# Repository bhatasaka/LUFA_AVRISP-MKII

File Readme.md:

# **LUFA AVRISP-MKII**

**Custom PCB designed for the LUFA AVRISP-MKII Project https://github.com/abcminiuser/lufa**

This repo contains the PCB and firmware configuration files for a compact USB-C programming board designed for LUFA's AVRISP-MKII firmware based on an ATMega16u2.  Major thanks to the LUFA project for making this possible!

<div align="center">

</div>

## About
---
This PCB is designed only for ISP. However, the PCB could be expanded to break out the PDI and TPI pins as well! It has a level shifter that allows programming of targets other than 5V. Adding a 2-pin jumper to `V Targ` allows the target device to be powered from this board as well. 2 voltages are available - 5v and 3.3v. If you wish to program the 16u2 from the ISP header, the RST pin must be shorted to the 16u2's RST pin, this can be done with a jumper on the `Self Prog` pin header.
## File Structure
---
- `Firmware`
    - Contains configuration files for the LUFA AVRISP-MKII project.
- `KiCad`
    - Contains the KiCad files for the PCB.
- `images`
    - Contains images of the PCB and schematic.

## Firmware Setup and Programming
---
### Setup
1. Clone the repository from https://github.com/abcminiuser/lufa.
1. From this repo's `Firmware` folder, copy and replace the `Config` folder and `makefile` into `Projects/AVRISP-MKII/` in the LUFA repo.
1. From this repo's `Firmware` folder, copy `BHATASAKA` folder into`LUFA/Divers/Board/AVR8` in the LUFA repo.
1. In the LUFA repo, modify `LUFA/Drivers/Board/Board.h` and copy the last `#elif`, then modify it to use `BHATASAKA` as the board name.
1. In the LUFA repo, modify `LUFA/Drivers/Board/LEDs.h` and copy the last `#elif`, then modify it to use `BHATASAKA` as the board name.

### Compiling
Go to `Projects/AVRISP-MKII/` and type `make`. Make sure Make and avr-gcc are installed and in your path.

### Programming
1. The hex file generated in the `Projects/AVRISP-MKII/` folder can be flashed through DFU. Plug the board into your computer. If it is blank it will show up as ATMega 16u2. If it doesn't, reset the chip after it's plugged in.
1. Download Zadig (https://zadig.akeo.ie/) and Atmel Flip (https://www.microchip.com/en-us/development-tool/flip) - make sure you Java SE JRE installed and in your path. Install Flip.
1. Open Zadig and select the 16u2. Install the `libusb-win32` driver for the chip.
1. Open Atmel Flip, select the 16u2, connect to it, load the hex file, and program the chip. It should now show up as an AVRISP-MKII (may need to unplug and replug).

## Usage
---
Install AVRISP-MKII drivers with Zadig (https://zadig.akeo.ie/). Choose `libusb-win32`.
To use with Arduino, select the `AVRISP mkii` programmer. To use with AVRDude, use `-c avrispmkII`.

---
Major thanks to LUFA, KiCad, and Zadig!

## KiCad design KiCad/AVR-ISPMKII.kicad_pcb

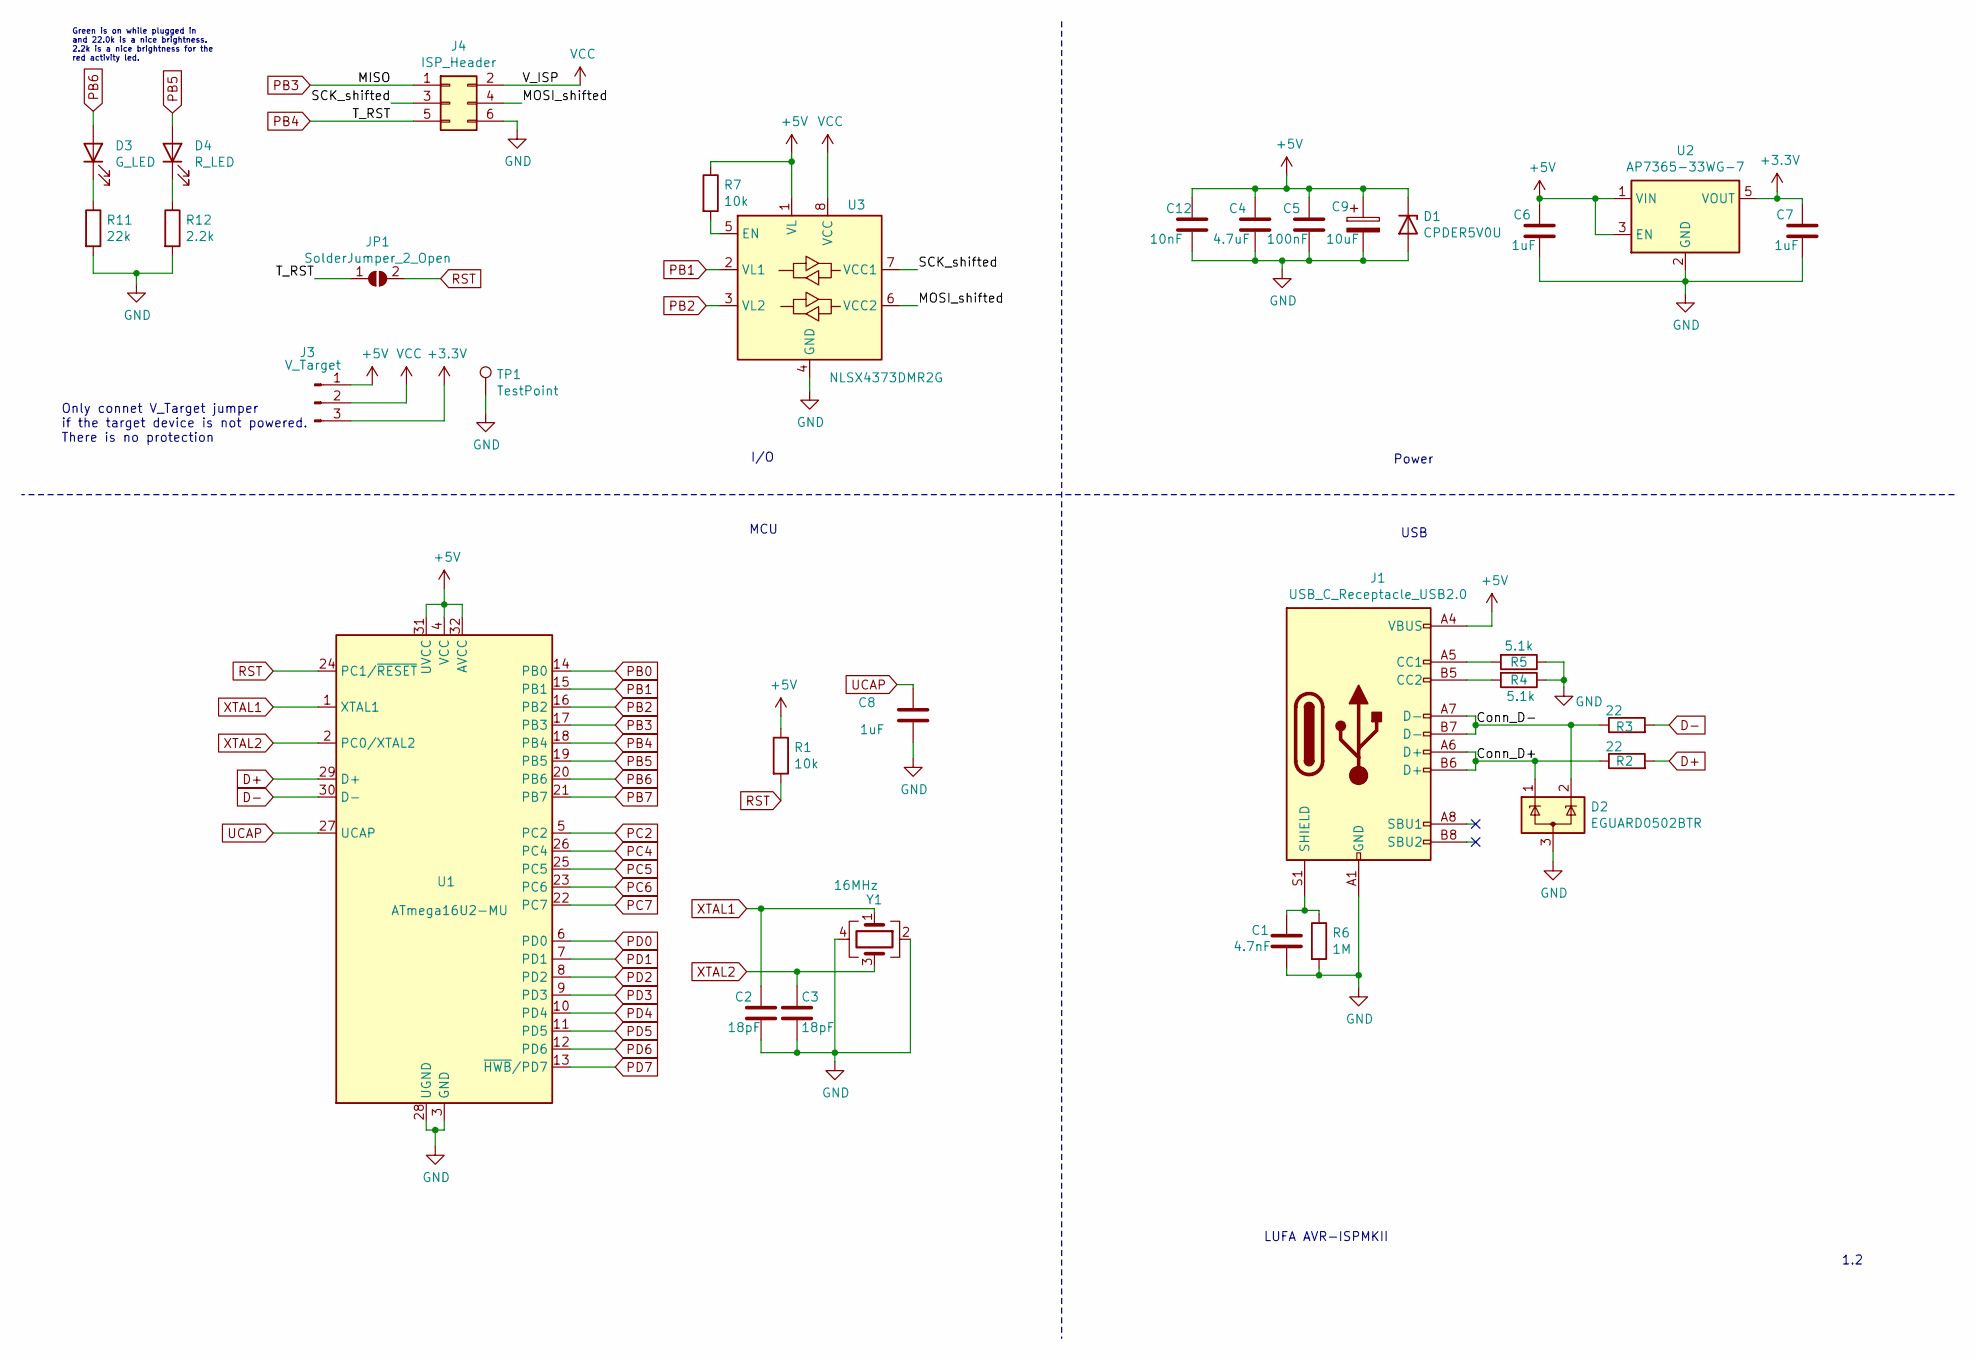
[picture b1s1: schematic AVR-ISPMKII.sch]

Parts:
C1: 4.7nF; C_0603_1608Metric
C2, C3: 18pF; C_0402_1005Metric
C4: 4.7uF; C_0805_2012Metric
C5: 100nF; C_0603_1608Metric
C6, C7, C8: 1uF; C_0603_1608Metric
C9: 10uF; C_0805_2012Metric
C12: 10nF; C_0603_1608Metric
D1: CPDER5V0U; D_0402_1005Metric
D2: EGUARD0502BTR; SOT-523
D3: G_LED; LED_0603_1608Metric
D4: R_LED; LED_0603_1608Metric
J1: USB_C_Receptacle_USB2.0; USB_C_Receptacle_HRO_TYPE-C-31-M-12
J3: V_Target; PinHeader_1x03_P2.54mm_Vertical
J4: ISP_Header; PinHeader_2x03_P2.54mm_Vertical
JP1: SolderJumper_2_Open; SolderJumper-2_P1.3mm_Open_TrianglePad1.0x1.5mm
R1, R7: 10k; R_0603_1608Metric
R2, R3: 22; R_0603_1608Metric
R4, R5: 5.1k; R_0603_1608Metric
R6: 1M; R_0603_1608Metric
R11: 22k; R_0603_1608Metric
R12: 2.2k; R_0603_1608Metric
TP1: TestPoint; TestPoint_Pad_D2.0mm
U1: ATmega16U2-MU; QFN-32-1EP_5x5mm_P0.5mm_EP3.1x3.1mm
U2: AP7365-33WG-7; TSOT-23-5
U3: NLSX4373DMR2G; TSSOP8
Y1: 16MHz; Crystal_SMD_2520-4Pin_2.5x2.0mm

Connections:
+3V3: C7.1, J3.3, U2.5 (VOUT)
+5V: C4.1, C5.1, C6.1, C9.1, C12.1, D1.1 (K), J1.A4 (VBUS), J1.A9 (VBUS), J1.B4 (VBUS), J1.B9 (VBUS), J3.1, R1.1, R7.1, U1.4 (VCC), U1.31 (UVCC), U1.32 (AVCC), U2.1 (VIN), U2.3 (EN), U3.1 (VL)
/Conn_D+: D2.1 (K), J1.A6 (D+), J1.B6 (D+), R2.1
/Conn_D-: D2.2 (K), J1.A7 (D-), J1.B7 (D-), R3.1
/MOSI_shifted: J4.4, U3.6 (VCC2)
/SCK_shifted: J4.3, U3.7 (VCC1)
D+: R2.2, U1.29 (D+)
D-: R3.2, U1.30 (D-)
GND: C1.2, C2.2, C3.2, C4.2, C5.2, C6.2, C7.2, C8.2, C9.2, C12.2, D1.2 (A), D2.3 (A), J1.A1 (GND), J1.A12 (GND), J1.B1 (GND), J1.B12 (GND), J4.6, R4.1, R5.1, R6.2, R11.2, R12.2, TP1.1, U1.3 (GND), U1.28 (UGND), U1.33 (GND), U2.2 (GND), U3.4 (GND), Y1.2, Y1.4
unnamed: C1.1, J1.S1 (SHIELD), R6.1
unnamed: D3.1 (K), R11.1
unnamed: D4.1 (K), R12.1
unnamed: J1.A5 (CC1), R5.2
unnamed: J1.B5 (CC2), R4.2
unnamed: R7.2, U3.5 (EN)
PB0: U1.14 (PB0)
PB1: U1.15 (PB1), U3.2 (VL1)
PB2: U1.16 (PB2), U3.3 (VL2)
PB3: J4.1, U1.17 (PB3)
PB4: J4.5, JP1.1 (A), U1.18 (PB4)
PB5: D4.2 (A), U1.19 (PB5)
PB6: D3.2 (A), U1.20 (PB6)
PB7: U1.21 (PB7)
PC2: U1.5 (PC2)
PC4: U1.26 (PC4)
PC5: U1.25 (PC5)
PC6: U1.23 (PC6)
PC7: U1.22 (PC7)
PD0: U1.6 (PD0)
PD1: U1.7 (PD1)
PD2: U1.8 (PD2)
PD3: U1.9 (PD3)
PD4: U1.10 (PD4)
PD5: U1.11 (PD5)
PD6: U1.12 (PD6)
PD7: U1.13 (~HWB~/PD7)
RST: JP1.2 (B), R1.2, U1.24 (PC1/~RESET)
UCAP: C8.1, U1.27 (UCAP)
VCC: J3.2, J4.2, U3.8 (VCC)
XTAL1: C2.1, U1.1 (XTAL1), Y1.1
XTAL2: C3.1, U1.2 (PC0/XTAL2), Y1.3

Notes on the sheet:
USB
MCU
I/O
Power
LUFA AVR-ISPMKII
Only connet V_Target jumper if the target device is not powered. There is no protection
1.2
Green is on while plugged in and 22.0k is a nice brightness. 2.2k is a nice brightness for the red activity led.

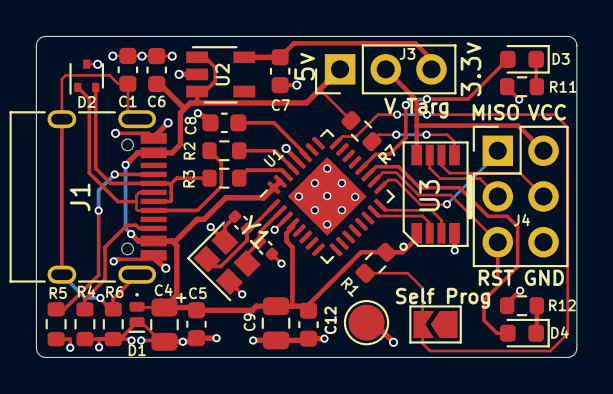
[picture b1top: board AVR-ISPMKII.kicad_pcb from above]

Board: 2 copper layers, 30.0 x 17.8 mm, 32 parts (0 on the bottom side), 26 nets.

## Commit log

2021-08-29 Initial commmit of PCB v1.2
2021-08-29 Updated LED resistors, corrected .gitignore
2021-09-12 Updated USB trace
2022-11-13 Corrected instructions to add the need to update LEDs.h in the LUFA repo
